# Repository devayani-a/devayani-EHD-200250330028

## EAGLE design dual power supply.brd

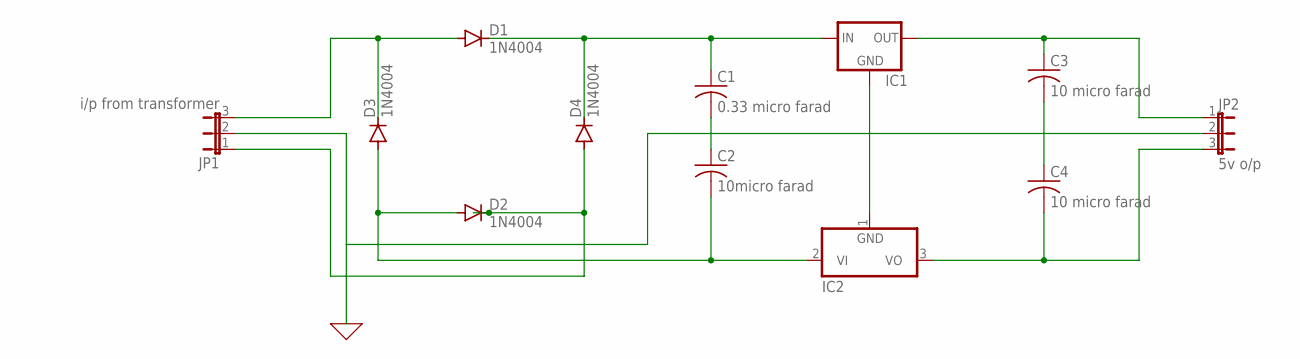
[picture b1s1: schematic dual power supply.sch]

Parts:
C1: 0.33 micro farad; C025-025X050
C2: 10micro farad; C025-025X050
C3, C4: 10 micro farad; C025-025X050
D1, D2, D3, D4: 1N4004; DO41-10
IC1: 78MXXS
IC2: 7905L; TO92
JP1: i/p from transformer; JP2
JP2: 5v o/p; JP2

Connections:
0: JP1.2, JP2.2
unnamed: D1.A, D3.C, JP1.3
unnamed: C1.1, D1.C, D4.C, IC1.IN
unnamed: D2.C, D4.A, JP1.1
unnamed: C1.2, C2.1
unnamed: C3.2, C4.1
unnamed: IC1.GND, IC2.1 (GND)
unnamed: C2.2, D2.A, D3.A, IC2.2 (VI)
unnamed: C3.1, IC1.OUT, JP2.1
unnamed: C4.2, IC2.3 (VO), JP2.3

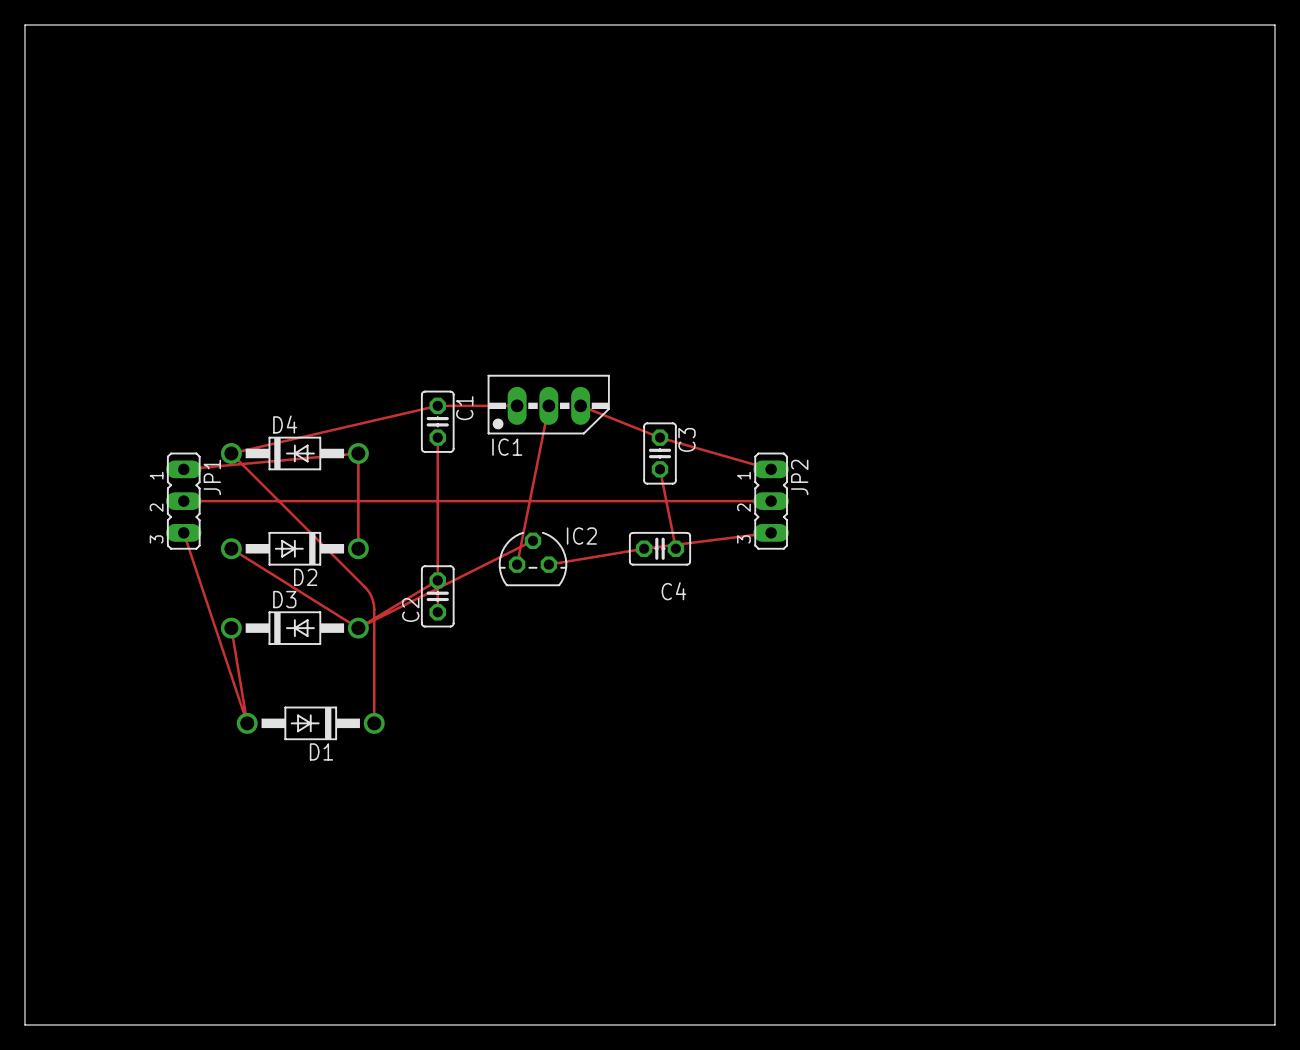
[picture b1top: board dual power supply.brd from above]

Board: 2 copper layers, 100.0 x 80.0 mm, 12 parts (0 on the bottom side), 10 nets.

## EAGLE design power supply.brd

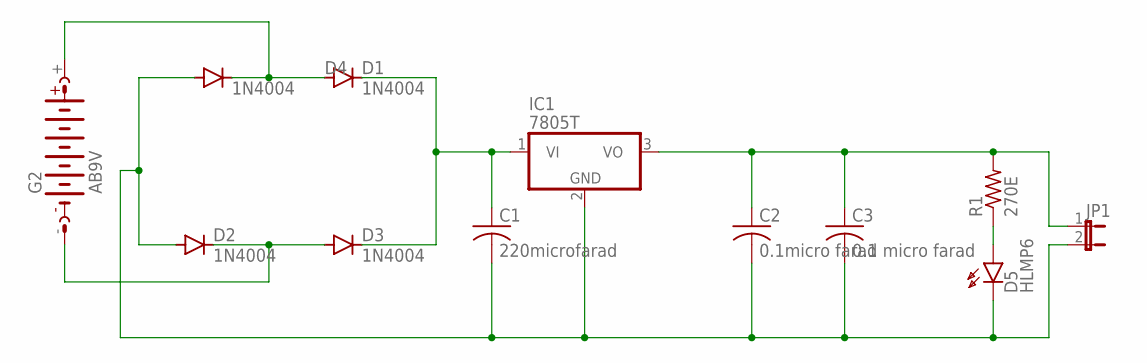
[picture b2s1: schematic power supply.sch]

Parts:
C1: 220microfarad; C050-030X075
C2: 0.1micro farad; C050-030X075
C3: 0.1 micro farad; C050-030X075
D1, D2, D3, D4: 1N4004; DO41-10
D5: HLMP6
G2: AB9V
IC1: 7805T; TO220H
JP1: JP1E; JP1
R1: 270E; 0204/7

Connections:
unnamed: D1.A, D4.C, G2.+
unnamed: D2.C, D3.A, G2.-
unnamed: C1.2, C2.2, C3.2, D2.A, D4.A, D5.K, IC1.2 (GND), JP1.2
unnamed: C1.1, D1.C, D3.C, IC1.1 (VI)
unnamed: C2.1, C3.1, IC1.3 (VO), JP1.1, R1.2
unnamed: D5.A, R1.1

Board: 2 copper layers, 12 parts (1 on the bottom side), 6 nets, no tracks yet.
